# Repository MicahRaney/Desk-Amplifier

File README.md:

All the desktop amps are either too cheap (passive), or too expensive (too many features).

This is a project to build the simplest version of what I need:
- 3 stereo line inputs
- Ability to change the volume per-input
- 1 line output
- No EQ changes noticable to listeners (below a 'Just Noticable Difference' [threshold](https://www.sciencedirect.com/topics/engineering/just-noticeable-difference))

## Design

To keep things cheap, the design uses a single op-amp per audio channel at the cost of crosstalk between inputs.

This is modified from a number of other similar projects/tutorials. Thank you, in particular, to:
 - https://www.youtube.com/watch?v=8ejBMXT3z2g
 - https://www.youtube.com/watch?v=-AFgLTBROns
 - https://www.youtube.com/watch?v=YCIcnFuRK7w

## PCB Render
Static render of the assembled PCB.

View this project on [CADLAB.io](https://cadlab.io/project/30623) to see the current Schematic / Board renders.

## Simulated Frequency Response
Frequency response using the TI OPAx134 SPICE models, and a 10kOhm output impedance device connected, at max volume for a single channel.

- Loss is < 306mdB throught the audible
- At maximum volume, the max gain is -175 mdB
- At 20hz, we see the largest damping at -306 mdB

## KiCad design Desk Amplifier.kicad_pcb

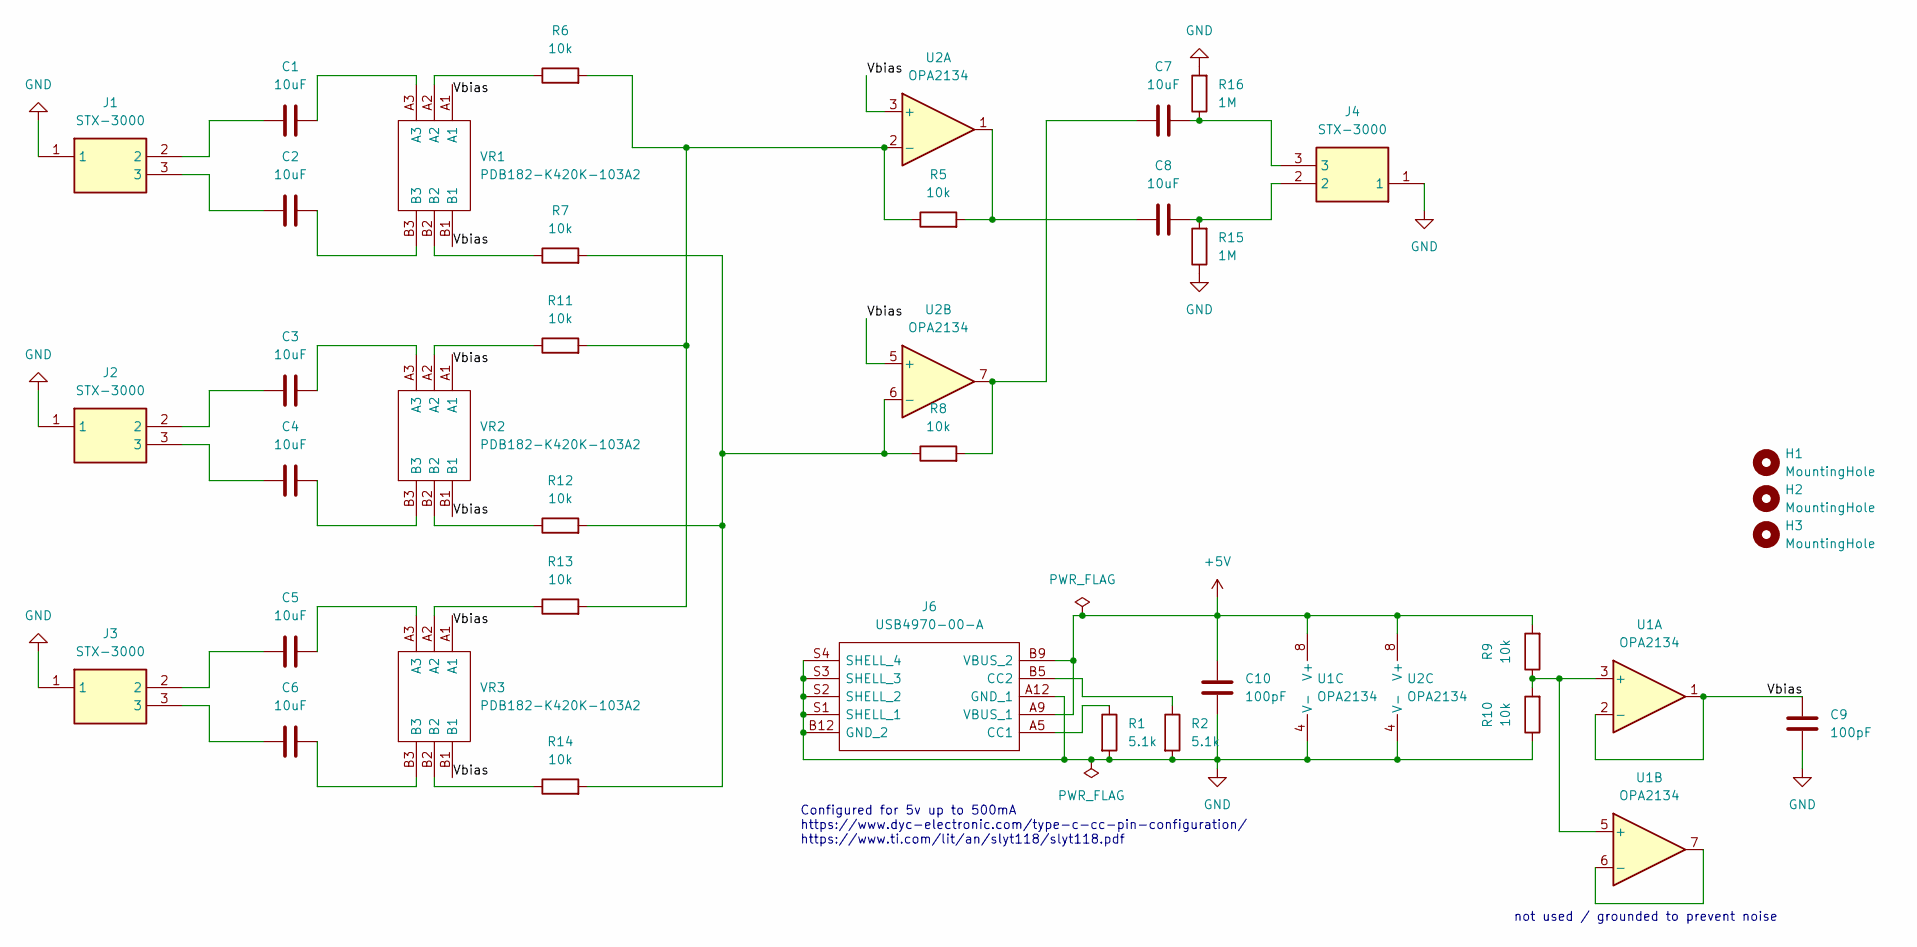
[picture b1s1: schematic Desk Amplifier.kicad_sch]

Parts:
C1, C2, C3, C4, C5, C6, C7, C8: 10uF; C_Disc_D5.0mm_W2.5mm_P2.50mm
C9, C10: 100pF; C_Disc_D5.0mm_W2.5mm_P2.50mm
H1, H2, H3: MountingHole; MountingHole_2.5mm
J1, J2, J3, J4: STX-3000; STX3000; Manufacturer_Part_Number STX-3000; Mouser Part Number 806-STX-3000
J6: USB4970-00-A; USB497000A; Manufacturer_Part_Number USB4970-00-A
R1, R2: 5.1k; R_Axial_DIN0207_L6.3mm_D2.5mm_P7.62mm_Horizontal
R5, R6, R7, R8, R9, R10, R11, R12, R13, R14: 10k; R_Axial_DIN0207_L6.3mm_D2.5mm_P7.62mm_Horizontal
R15, R16: 1M; R_Axial_DIN0207_L6.3mm_D2.5mm_P7.62mm_Horizontal
U1, U2: OPA2134; DIP-8_W7.62mm
VR1, VR2, VR3: PDB182-K420K-103A2; PDB182K420P204A2; Manufacturer_Part_Number PDB182-K420K-103A2; Mouser Part Number 652-PDB182K420K103A2

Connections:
+5V: C10.2, J6.A9 (VBUS_1), J6.B9 (VBUS_2), R9.2, U1.8 (V+), U2.8 (V+)
/Vbias: C9.2, U1.1, U1.2 (-), U2.3 (+), U2.5 (+), VR1.A1, VR1.B1, VR2.A1, VR2.B1, VR3.A1, VR3.B1
GND: C9.1, C10.1, J1.1, J2.1, J3.1, J4.1, J6.A12 (GND_1), J6.B12 (GND_2), J6.S1 (SHELL_1), J6.S2 (SHELL_2), J6.S3 (SHELL_3), J6.S4 (SHELL_4), R1.2, R2.2, R10.1, R15.1, R16.2, U1.4 (V-), U2.4 (V-)
unnamed: C1.1, J1.2
unnamed: C1.2, VR1.A3
unnamed: C2.1, J1.3
unnamed: C2.2, VR1.B3
unnamed: C3.1, J2.2
unnamed: C3.2, VR2.A3
unnamed: C4.1, J2.3
unnamed: C4.2, VR2.B3
unnamed: C5.1, J3.2
unnamed: C5.2, VR3.A3
unnamed: C6.1, J3.3
unnamed: C6.2, VR3.B3
unnamed: C7.1, R8.2, U2.7
unnamed: C7.2, J4.3, R16.1
unnamed: C8.1, R5.2, U2.1
unnamed: C8.2, J4.2, R15.2
unnamed: J6.A5 (CC1), R1.1
unnamed: J6.B5 (CC2), R2.1
unnamed: R6.1, VR1.A2
unnamed: R7.1, VR1.B2
unnamed: R11.1, VR2.A2
unnamed: R12.1, VR2.B2
unnamed: R13.1, VR3.A2
unnamed: R14.1, VR3.B2
unnamed: R9.1, R10.2, U1.3 (+), U1.5 (+)
unnamed: U1.6 (-), U1.7
unnamed: R5.1, R6.2, R11.2, R13.2, U2.2 (-)
unnamed: R7.2, R8.1, R12.2, R14.2, U2.6 (-)

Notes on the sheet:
not used / grounded to prevent noise
Configured for 5v up to 500mA https://www.dyc-electronic.com/type-c-cc-pin-configuration/ https://www.ti.com/lit/an/slyt118/slyt118.pdf

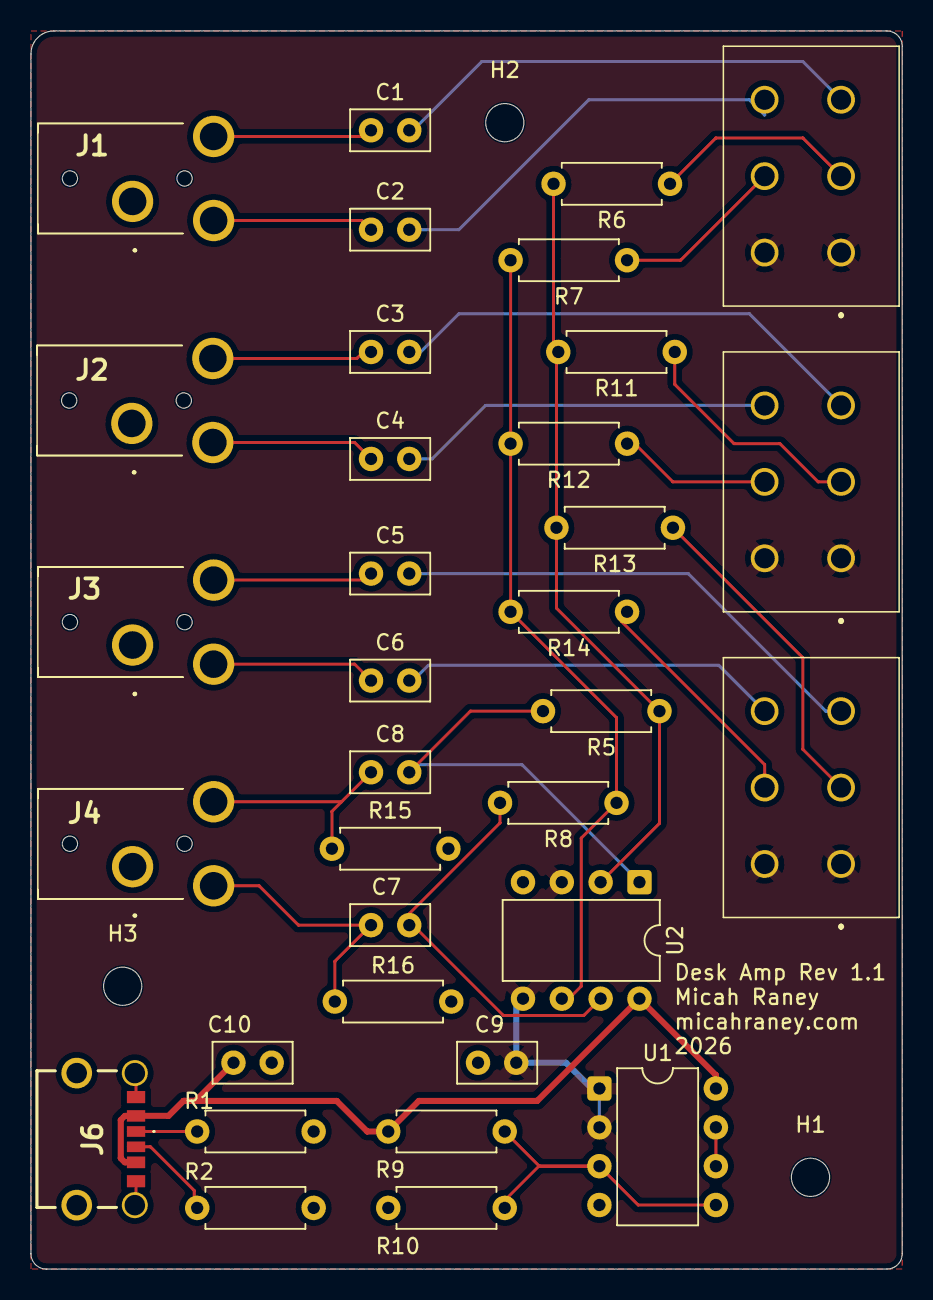
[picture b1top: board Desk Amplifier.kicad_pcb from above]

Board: 2 copper layers, 57.0 x 81.0 mm, 37 parts (0 on the bottom side), 31 nets.
